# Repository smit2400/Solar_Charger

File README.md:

# Heavy-Duty Solar Charge Controller

A solar charge controller for a **24 V, 100 Ah** battery bank, built around a **PIC16F676** microcontroller with 60 V / 40 A **TK40E06N1** power MOSFETs and wide copper for high charging currents. The MCU monitors the panel and battery, switches the charge path, and powers a switchable DC load. Back-to-back MOSFETs stop the battery draining into the panel at night. Developed at Shriji Technoaspire in 2022.

*2-layer, 65 × 84 mm (rendered from the KiCad layout)*

---

## Key specs

| | |
|---|---|
| **Battery** | 24 V, 100 Ah |
| **MCU** | Microchip PIC16F676 (14-pin SOIC, 10-bit ADC) |
| **Power switches** | 3 × Toshiba TK40E06N1 N-MOSFETs (60 V, 40 A, TO-220) |
| **Switching** | Low-side, common-positive (panel, battery and load share +ve) |
| **Reverse blocking** | Back-to-back MOSFET pair on the solar input |
| **Logic supply** | Transistor and Zener pre-regulator into a 78L05 5 V regulator |
| **Connections** | Screw terminals for solar, battery and load; 5-pin programming/status header |
| **Indicators** | 3 status LEDs, reset button |
| **PCB** | 2 layers, 65 × 84 mm, power traces up to 1.5 mm, KiCad 6 |

## How it works

```
 Solar +ve ─────────────────────────┬────────────────────┬──────── Load +ve
                                    │                    │
                                Battery +ve          PIC16F676 ◄── voltage sense
                                    │                    │
 Solar -ve ──[M3]◄►[M2]── Battery -ve ──[M1]── Load -ve  │
              charge switch          load switch         │
                  ▲                       ▲              │
                  └──── gate drive ───────┴──────────────┘
```

**Charge path.** M2 and M3 are N-MOSFETs with their sources tied together, placed between the panel and battery negatives. Back to back, their body diodes face opposite ways, so when they're off no current flows in either direction. This blocks the battery from discharging into the panel at night, which a single MOSFET can't do. A transistor driver (Q5, Q6) switches the shared gate, and a 12 V Zener (Z2) clamps the gate-source voltage.

**Load path.** M1 switches the load negative. Its gate is driven by the PIC through a 100 Ω gate resistor, so the MCU can disconnect the load. The output is general-purpose and was used with different DC loads, not only lighting.

**Sensing.** Resistor dividers bring the battery and panel voltages into the PIC's analog inputs.

**Supply.** The 78L05 is fed from the battery through a Zener-referenced transistor pre-regulator (Q2, Z3). The 12 V Zener drops the 24 V battery to a safe input for the 78L05, which gives the MCU a clean 5 V rail.

**Firmware.** The PIC16F676 firmware is not included in this repository.

**Layout choices.**
- Through-hole TO-220 MOSFETs for current handling.
- High-current paths routed as 1.0–1.5 mm traces.
- The MCU and sensing circuitry sit at the opposite end of the board from the power terminals.

## Repository structure

```
Solar_Charger/
├── hardware/
│   ├── Solar_Charge_Controller.kicad_pro   KiCad 6 project
│   ├── Solar_Charge_Controller.kicad_sch   Schematic
│   ├── Solar_Charge_Controller.kicad_pcb   PCB layout
│   ├── Solar_Charge_Controller_BOM.csv     Bill of materials
│   └── fabrication/                        Gerbers + drill files (.zip)
└── docs/images/                            Board render
```

Open `hardware/Solar_Charge_Controller.kicad_pro` in **KiCad 6** or newer.

## Tools

KiCad 6 · Microchip PIC16F676

## Acknowledgements

Thanks to **Dhruvil Patel**, my supervisor at Shriji Technoaspire, for mentoring me through this project.

## License

No license is granted. This repository is shared as a portfolio of my work; all rights reserved.

---

**Smit Vaghela** — Embedded Software / Firmware Engineer · [GitHub](https://github.com/smit2400)

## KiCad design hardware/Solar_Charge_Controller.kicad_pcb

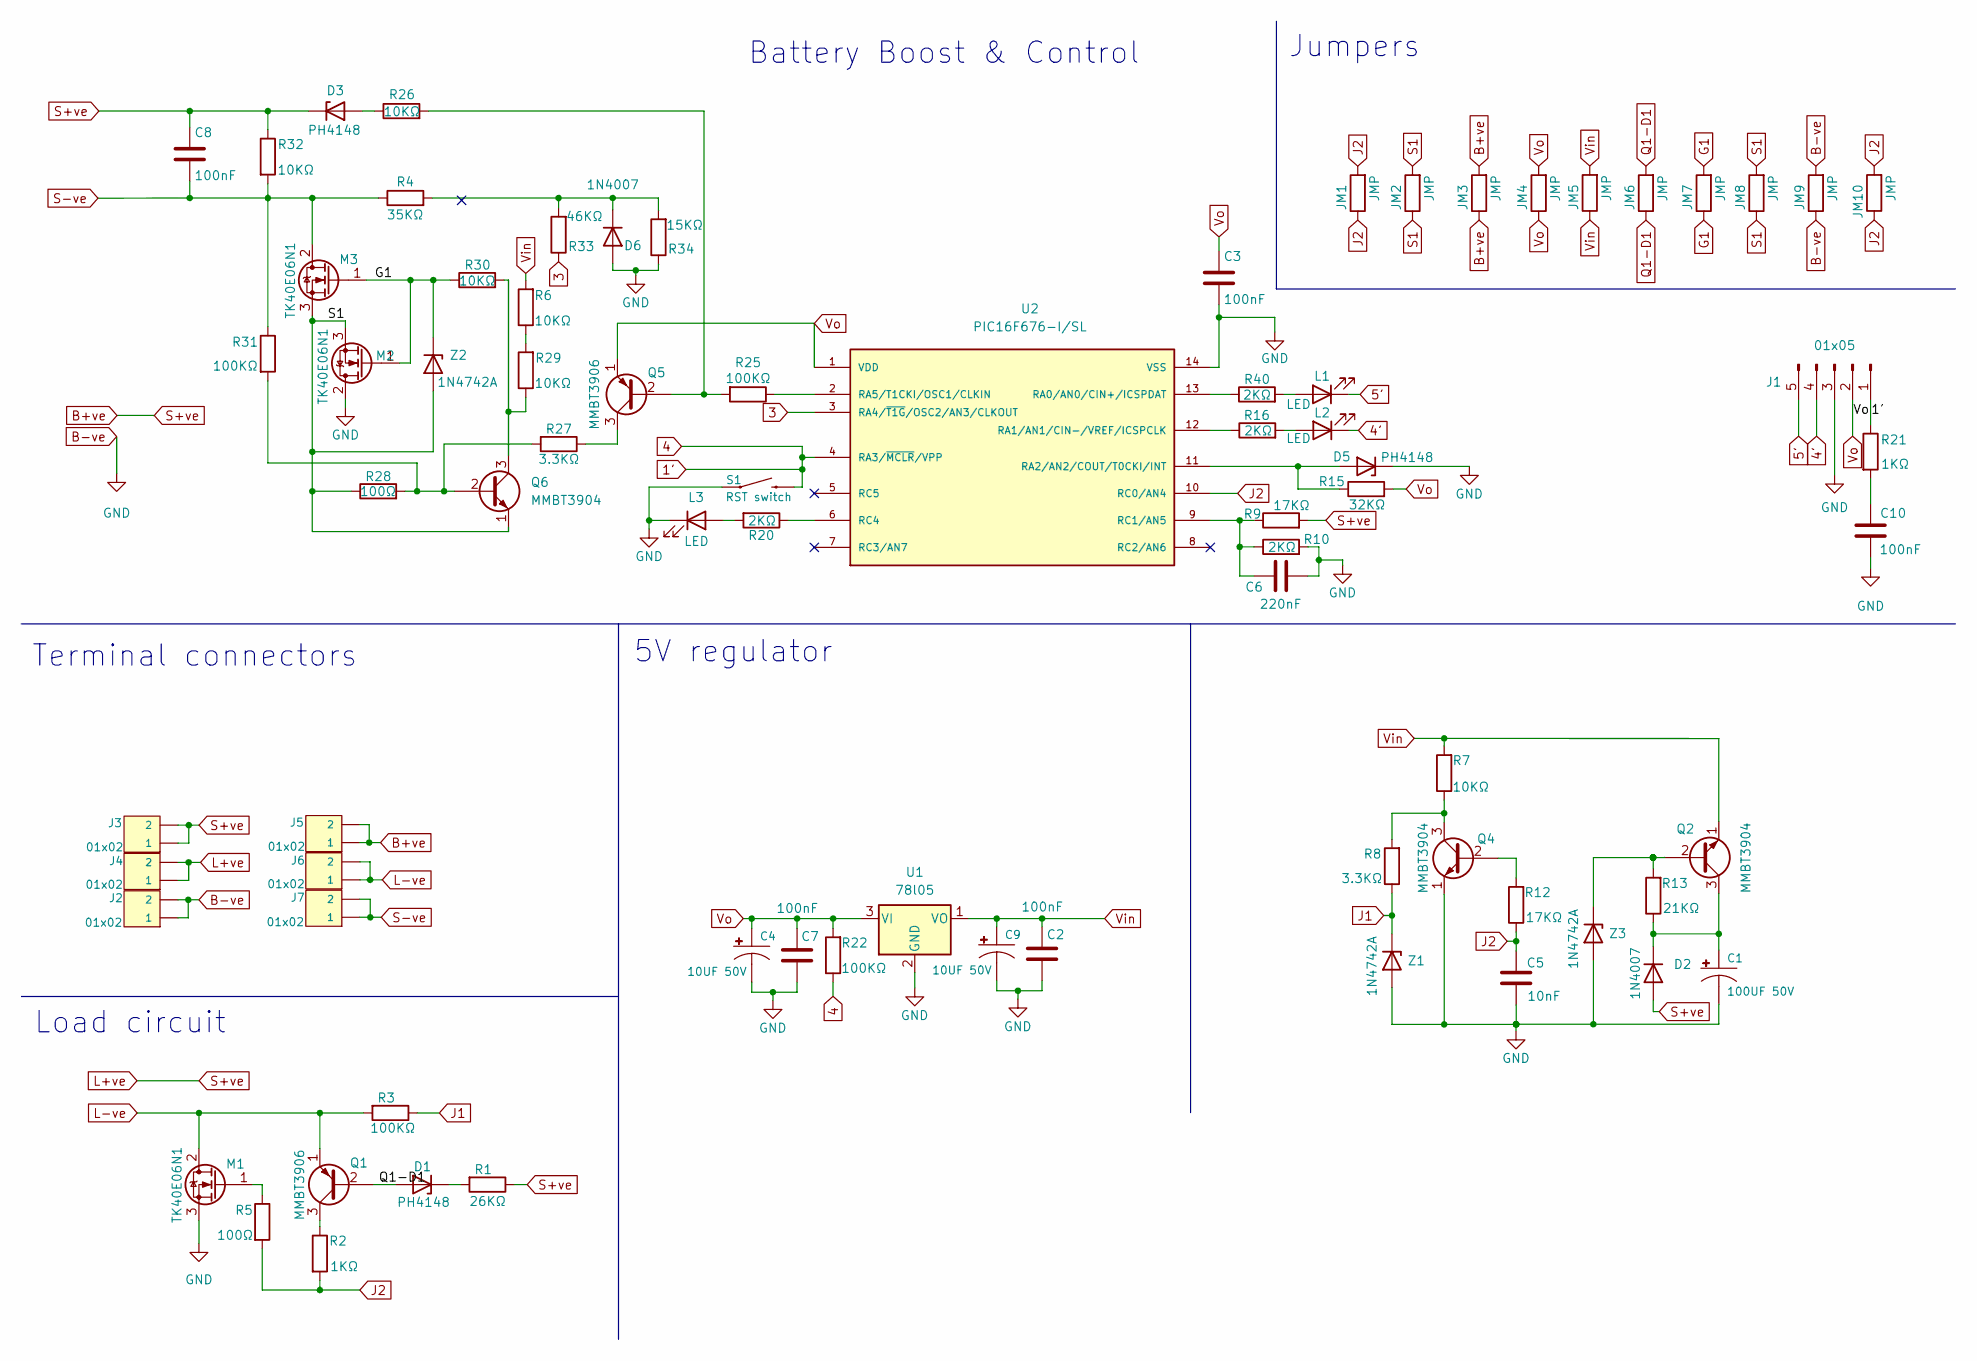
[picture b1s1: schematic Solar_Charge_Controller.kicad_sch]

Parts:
C1: 100UF 50V; CP_Radial_D5.0mm_P2.50mm
C2, C3, C7, C8, C10: 100nF; 1206
C4, C9: 10UF 50V; CP_Radial_D5.0mm_P2.50mm
C5: 10nF; 1206
C6: 220nF; 1206
D1, D3, D5: PH4148; 1210
D2, D6: 1N4007; 1210
J1: 01x05; 1X05
J2, J3, J4, J5, J6, J7: 01x02; TE_282837-2
JM1: JMP; 1206
JM2, JM3, JM4, JM5, JM6, JM7, JM8, JM9, JM10: JMP; DIODE-1N4001
L1, L2, L3: LED; LED_5MM
M1, M2, M3: TK40E06N1; TO220V
Q1, Q5: MMBT3906; SOT23-3
Q2, Q4, Q6: MMBT3904; SOT23-3
R1: 26KΩ; 1206
R2, R21: 1KΩ; 1206
R3, R22, R25, R31: 100KΩ; 1206
R4: 35KΩ; 1206
R5, R28: 100Ω; 1206
R6, R7, R26, R29, R30, R32: 10KΩ; 1206
R8, R27: 3.3KΩ; 1206
R9, R12: 17KΩ; 1206
R10, R16, R20, R40: 2KΩ; 1206
R13: 21KΩ; 1206
R15: 32KΩ; 1206
R33: 46KΩ; 1206
R34: 15KΩ; 1206
S1: RST switch; TACTILE_SWITCH_PTH_6.0MM
U1: 78l05; SOT89R
U2: PIC16F676-I/SL; SOIC127P600X175-14N
Z1, Z3: 1N4742A; 1210
Z2: 1N4742A; DIODE-1N4001

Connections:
1': J1.1, R21.1, R22.1, S1.3 (2), U2.4 (RA3/~MCLR/VPP)
3: R33.1, U2.3 (RA4/~T1G/OSC2/AN3/CLKOUT)
4': J1.4, L2.1 (K)
5': J1.5, L1.1 (K)
B+ve: C8.1, D2.2 (A), D3.1 (K), J3.1, J3.2, J4.1, J4.2, J5.1, J5.2, JM3.1, JM3.2, R1.1, R9.2, R32.1
B-ve: C2.1, C3.2, C4.2 (-), C6.2, C7.1, C9.2 (-), C10.1, D5.1 (K), D6.2 (A), J1.3, J2.1, J2.2, JM9.1, JM9.2, L3.1 (K), M1.3 (S), M2.2 (D), R10.2, R34.1, S1.1, U1.2 (GND), U2.14 (VSS)
G1: JM7.1, JM7.2, M2.1 (G), M3.1 (G), R30.1, Z2.1 (K)
J1: R3.1, R8.1, Z1.1 (K)
J2: C5.2, JM1.1, JM1.2, JM10.1, JM10.2, R2.2, R5.2, R12.1, U2.10 (RC0/AN4)
L-ve: J6.1, J6.2, M1.2 (D), Q1.1 (E), R3.2
unnamed: C1.1 (+), D2.1 (K), Q2.3 (C), R13.1
unnamed: C1.2 (-), C5.1, Q4.1 (E), Z1.2 (A), Z3.2 (A)
unnamed: C6.1, R9.1, R10.1, U2.9 (RC1/AN5)
unnamed: C10.2, R21.2
unnamed: D1.1 (K), R1.2
unnamed: D3.2 (A), R26.1
unnamed: D5.2 (A), R15.1, U2.11 (RA2/AN2/COUT/T0CKI/INT)
unnamed: D6.1 (K), R4.2, R33.2, R34.2
unnamed: L1.2 (A), R40.2
unnamed: L2.2 (A), R16.2
unnamed: L3.2 (A), R20.2
unnamed: M1.1 (G), R5.1
unnamed: Q1.3 (C), R2.1
unnamed: Q2.2 (B), R13.2, Z3.1 (K)
unnamed: Q4.2 (B), R12.2
unnamed: Q4.3 (C), R7.1, R8.2
unnamed: Q5.2 (B), R25.2, R26.2
unnamed: Q5.3 (C), R27.1
unnamed: Q6.2 (B), R27.2, R28.2, R31.2
unnamed: Q6.3 (C), R29.1, R30.2
unnamed: R16.1, U2.12 (RA1/AN1/CIN-/VREF/ICSPCLK)
unnamed: R20.1, U2.6 (RC4)
unnamed: R25.1, U2.2 (RA5/T1CKI/OSC1/CLKIN)
unnamed: R6.1, R29.2
unnamed: R40.1, U2.13 (RA0/AN0/CIN+/ICSPDAT)
Q1-D1: D1.2 (A), JM6.1, JM6.2, Q1.2 (B)
S1: JM2.1, JM2.2, JM8.1, JM8.2, M2.3 (S), M3.3 (S), Q6.1 (E), R28.1, Z2.2 (A)
S-ve: C8.2, J7.1, J7.2, M3.2 (D), R4.1, R31.1, R32.2
Vin: C2.2, C9.1 (+), JM5.1, JM5.2, Q2.1 (E), R6.2, R7.2, U1.1 (VO)
Vo: C3.1, C4.1 (+), C7.2, J1.2, JM4.1, JM4.2, Q5.1 (E), R15.2, R22.2, U1.3 (VI), U2.1 (VDD)

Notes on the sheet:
Load circuit
Battery Boost & Control
5V regulator
Jumpers
Terminal connectors

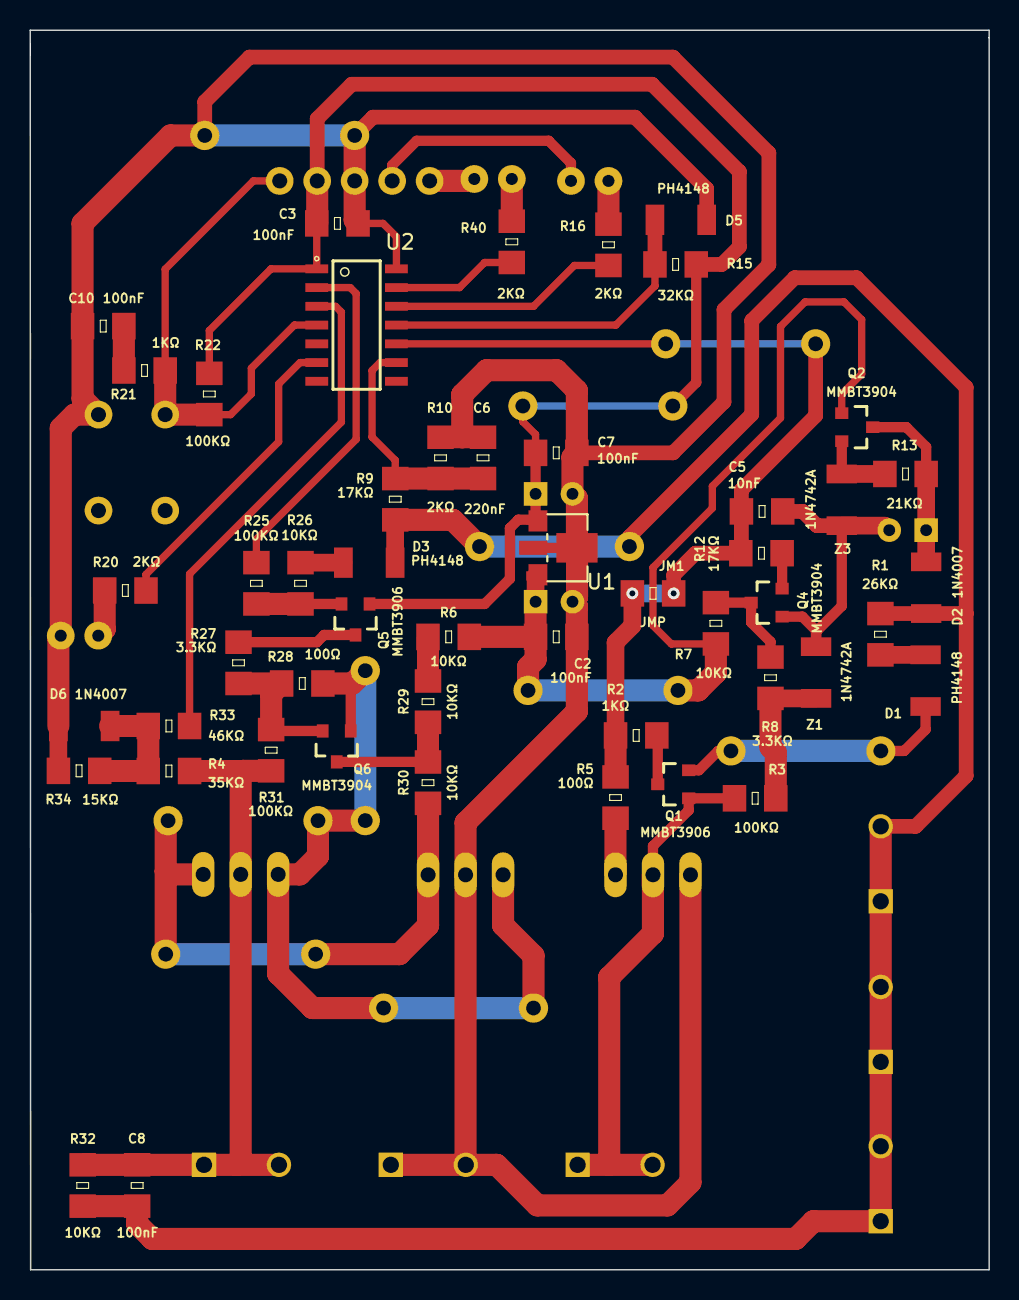
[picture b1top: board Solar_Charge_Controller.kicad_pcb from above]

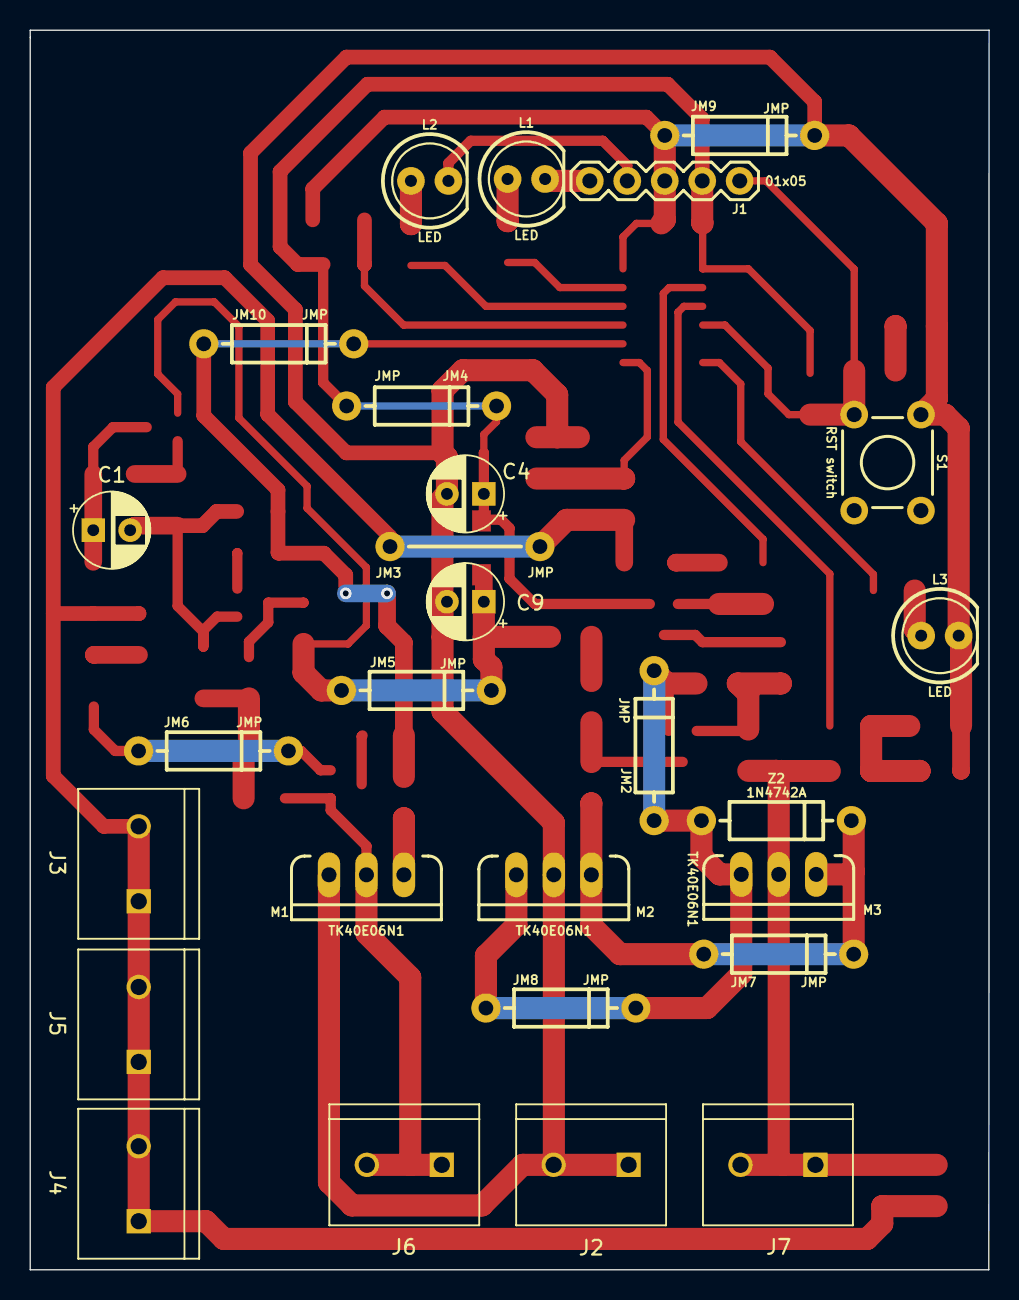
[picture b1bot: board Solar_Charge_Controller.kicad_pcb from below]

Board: 2 copper layers, 65.0 x 84.0 mm, 77 parts (27 on the bottom side), 40 nets.

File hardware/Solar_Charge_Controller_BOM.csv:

Item,References,Qty,Value,Footprint
1,C1,1,100UF 50V,CP_Radial_D5.0mm_P2.50mm
2,"C2, C3, C7, C8, C10",5,100nF,1206
3,"C4, C9",2,10UF 50V,CP_Radial_D5.0mm_P2.50mm
4,C5,1,10nF,1206
5,C6,1,220nF,1206
6,"D1, D3, D5",3,PH4148,1210
7,"D2, D6",2,1N4007,1210
8,J1,1,01x05,1X05
9,"J2, J3, J4, J5, J6, J7",6,01x02,TE_282837-2
10,JM1,1,JMP,1206
11,"JM2, JM3, JM4, JM5, JM6, JM7, JM8, JM9, JM10",9,JMP,DIODE-1N4001
12,"L1, L2, L3",3,LED,LED_5MM
13,"M1, M2, M3",3,TK40E06N1,TO220V
14,"Q1, Q5",2,MMBT3906,SOT23-3
15,"Q2, Q4, Q6",3,MMBT3904,SOT23-3
16,R1,1,26KΩ,1206
17,"R2, R21",2,1KΩ,1206
18,"R3, R22, R25, R31",4,100KΩ,1206
19,R4,1,35KΩ,1206
20,"R5, R28",2,100Ω,1206
21,"R6, R7, R26, R29, R30, R32",6,10KΩ,1206
22,"R8, R27",2,3.3KΩ,1206
23,"R9, R12",2,17KΩ,1206
24,"R10, R16, R20, R40",4,2KΩ,1206
25,R13,1,21KΩ,1206
26,R15,1,32KΩ,1206
27,R33,1,46KΩ,1206
28,R34,1,15KΩ,1206
29,S1,1,RST switch,TACTILE_SWITCH_PTH_6.0MM
30,U1,1,78l05,SOT89R
31,U2,1,PIC16F676-I/SL,SOIC127P600X175-14N
32,"Z1, Z3",2,1N4742A,1210
33,Z2,1,1N4742A,DIODE-1N4001
